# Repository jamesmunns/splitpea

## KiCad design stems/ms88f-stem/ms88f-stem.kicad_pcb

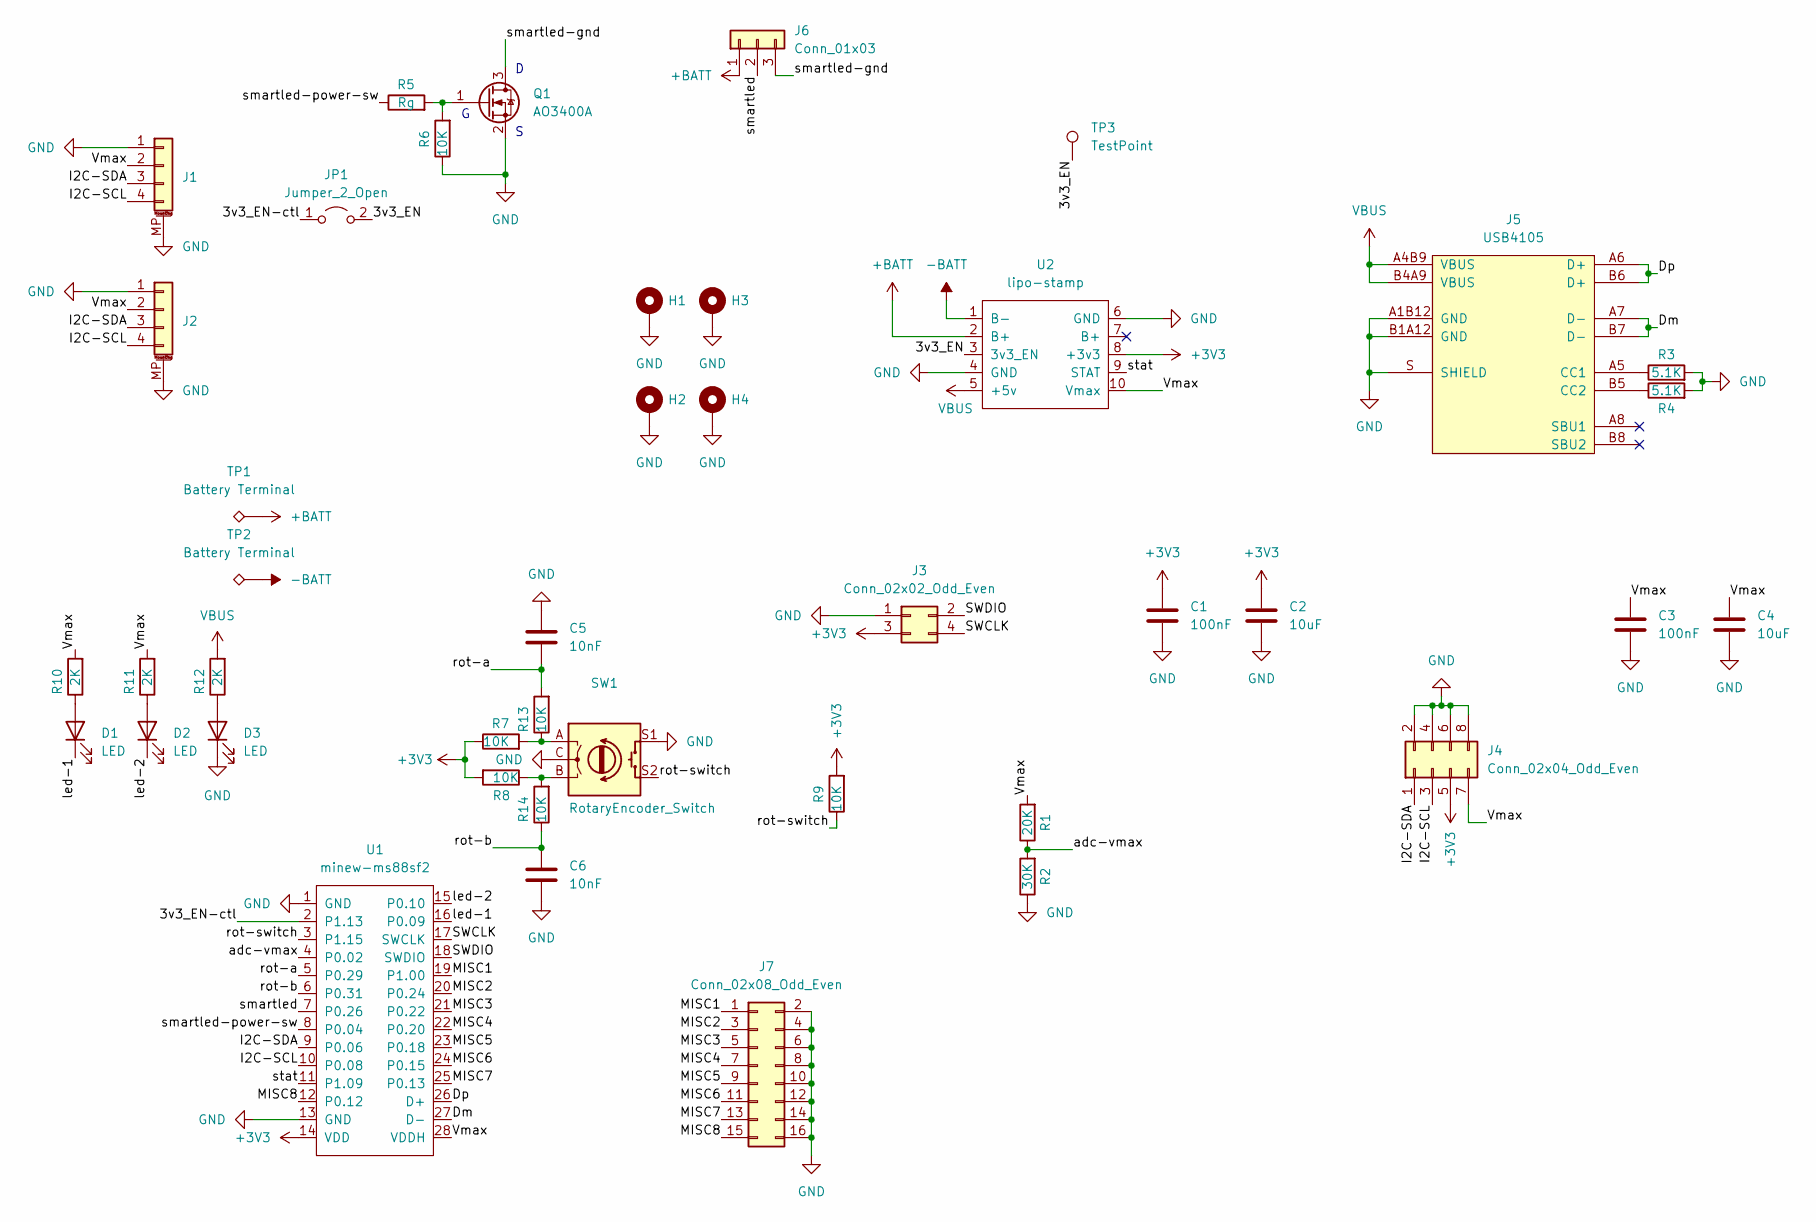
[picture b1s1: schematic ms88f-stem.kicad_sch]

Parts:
C1, C3: 100nF; C_0805_2012Metric
C2, C4: 10uF; C_0805_2012Metric
C5, C6: 10nF; C_0805_2012Metric
D1, D2, D3: LED; LED_0805_2012Metric
H1, H2, H3, H4: MountingHole_Pad; MountingHole_3.2mm_M3_Pad_Via
J1, J2: Conn_01x04_MountingPin; JST_SH_SM04B-SRSS-TB_1x04-1MP_P1.00mm_Horizontal
J3: Conn_02x02_Odd_Even; PinHeader_2x02_P2.54mm_Vertical_SMD
J4: Conn_02x04_Odd_Even; PinHeader_2x04_P2.54mm_Vertical
J5: USB4105; DigiKey 2073-USB4105-GF-ACT-ND
J6: Conn_01x03; PinHeader_1x03_P2.54mm_Horizontal
J7: Conn_02x08_Odd_Even; PinHeader_2x08_P2.54mm_Vertical
JP1: Jumper_2_Open; SolderJumper-2_P1.3mm_Open_TrianglePad1.0x1.5mm
Q1: AO3400A; SOT-23
R1: 20K; R_0805_2012Metric
R2: 30K; R_0805_2012Metric
R3, R4: 5.1K; R_0805_2012Metric
R5: Rg; R_0805_2012Metric
R6, R7, R8, R9, R13, R14: 10K; R_0805_2012Metric
R10, R11, R12: 2K; R_0805_2012Metric
SW1: RotaryEncoder_Switch; RotaryEncoder_Alps_EC11E-Switch_Vertical_H20mm
TP1, TP2: Battery Terminal; keystone-54
TP3: TestPoint; TestPoint_Pad_1.5x1.5mm
U1: minew-ms88sf2; minew-MS88SF21
U2: lipo-stamp

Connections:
+3V3: C1.1, C2.1, J3.3, J4.5, R7.1, R8.2, R9.2, U1.14 (VDD), U2.8 (+3v3)
+BATT: J6.1, TP1.1, U2.2 (B+)
-BATT: TP2.1, U2.1 (B-)
/3v3_EN: JP1.2 (B), TP3.1, U2.3 (3v3_EN)
/3v3_EN-ctl: JP1.1 (A), U1.2 (P1.13)
/Dm: J5.A7 (D-), J5.B7 (D-), U1.27 (D-)
/Dp: J5.A6 (D+), J5.B6 (D+), U1.26 (D+)
/I2C-SCL: J1.4, J2.4, J4.3, U1.10 (P0.08)
/I2C-SDA: J1.3, J2.3, J4.1, U1.9 (P0.06)
/MISC1: J7.1, U1.19 (P1.00)
/MISC2: J7.3, U1.20 (P0.24)
/MISC3: J7.5, U1.21 (P0.22)
/MISC4: J7.7, U1.22 (P0.20)
/MISC5: J7.9, U1.23 (P0.18)
/MISC6: J7.11, U1.24 (P0.15)
/MISC7: J7.13, U1.25 (P0.13)
/MISC8: J7.15, U1.12 (P0.12)
/SWCLK: J3.4, U1.17 (SWCLK)
/SWDIO: J3.2, U1.18 (SWDIO)
/Vmax: C3.1, C4.1, J1.2, J2.2, J4.7, R1.2, R10.2, R11.2, U1.28 (VDDH), U2.10 (Vmax)
/adc-vmax: R1.1, R2.2, U1.4 (P0.02)
/led-1: D1.1 (K), U1.16 (P0.09)
/led-2: D2.1 (K), U1.15 (P0.10)
/rot-a: C5.1, R13.2, U1.5 (P0.29)
/rot-b: C6.1, R14.1, U1.6 (P0.31)
/rot-switch: R9.1, SW1.S2, U1.3 (P1.15)
/smartled: J6.2, U1.7 (P0.26)
/smartled-gnd: J6.3, Q1.3 (D)
/smartled-power-sw: R5.1, U1.8 (P0.04)
/stat: U1.11 (P1.09), U2.9 (STAT)
GND: C1.2, C2.2, C3.2, C4.2, C5.2, C6.2, D3.1 (K), H1.1, H2.1, H3.1, H4.1, J1.1, J1.MP (MountPin), J2.1, J2.MP (MountPin), J3.1, J4.2, J4.4, J4.6, J4.8, J5.A1B12 (GND), J5.B1A12 (GND), J5.S (SHIELD), J7.2, J7.4, J7.6, J7.8, J7.10, J7.12, J7.14, J7.16, Q1.2 (S), R2.1, R3.2, R4.2, R6.1, SW1.C, SW1.S1, U1.1 (GND), U1.13 (GND), U2.4 (GND), U2.6 (GND)
unnamed: D1.2 (A), R10.1
unnamed: D2.2 (A), R11.1
unnamed: D3.2 (A), R12.1
unnamed: J5.A5 (CC1), R3.1
unnamed: J5.B5 (CC2), R4.1
unnamed: Q1.1 (G), R5.2, R6.2
unnamed: R7.2, R13.1, SW1.A
unnamed: R8.1, R14.2, SW1.B
VBUS: J5.A4B9 (VBUS), J5.B4A9 (VBUS), R12.2, U2.5 (+5v)

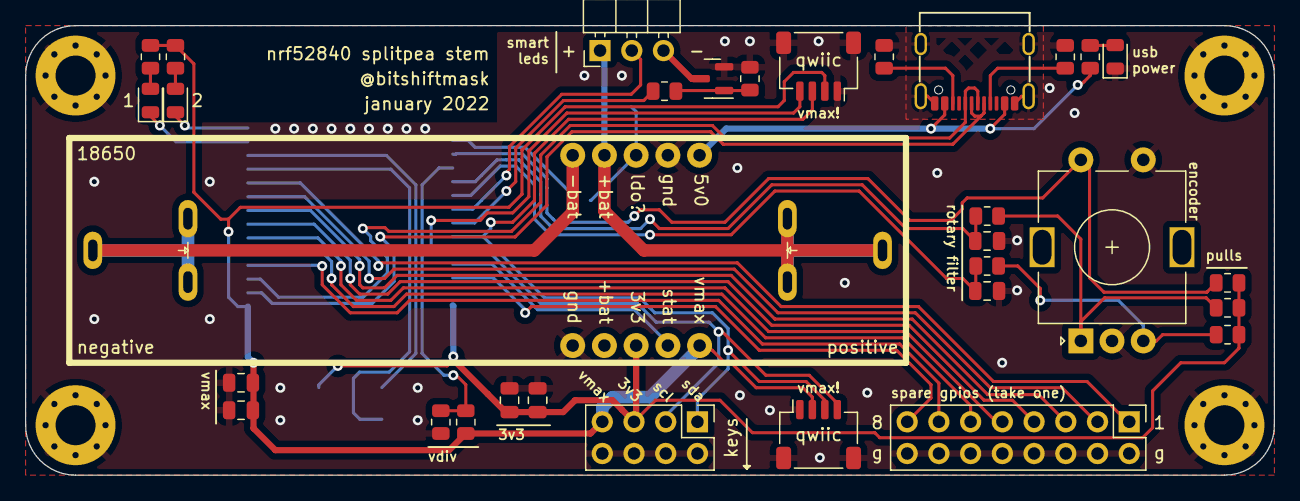
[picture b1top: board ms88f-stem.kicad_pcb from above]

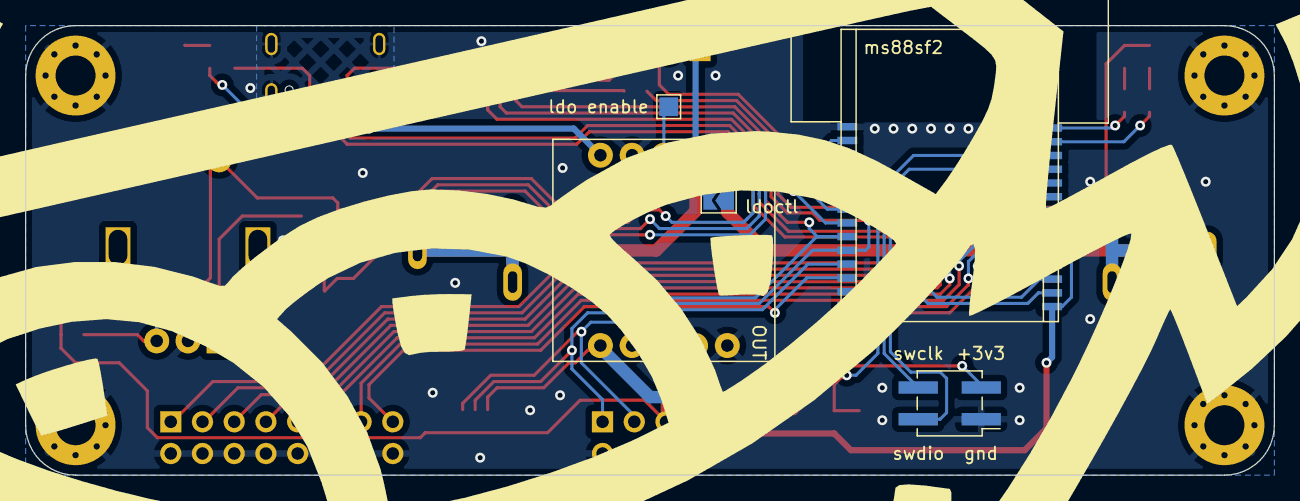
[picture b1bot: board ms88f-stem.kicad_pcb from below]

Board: 2 copper layers, 100.0 x 36.0 mm, 42 parts (5 on the bottom side), 40 nets.

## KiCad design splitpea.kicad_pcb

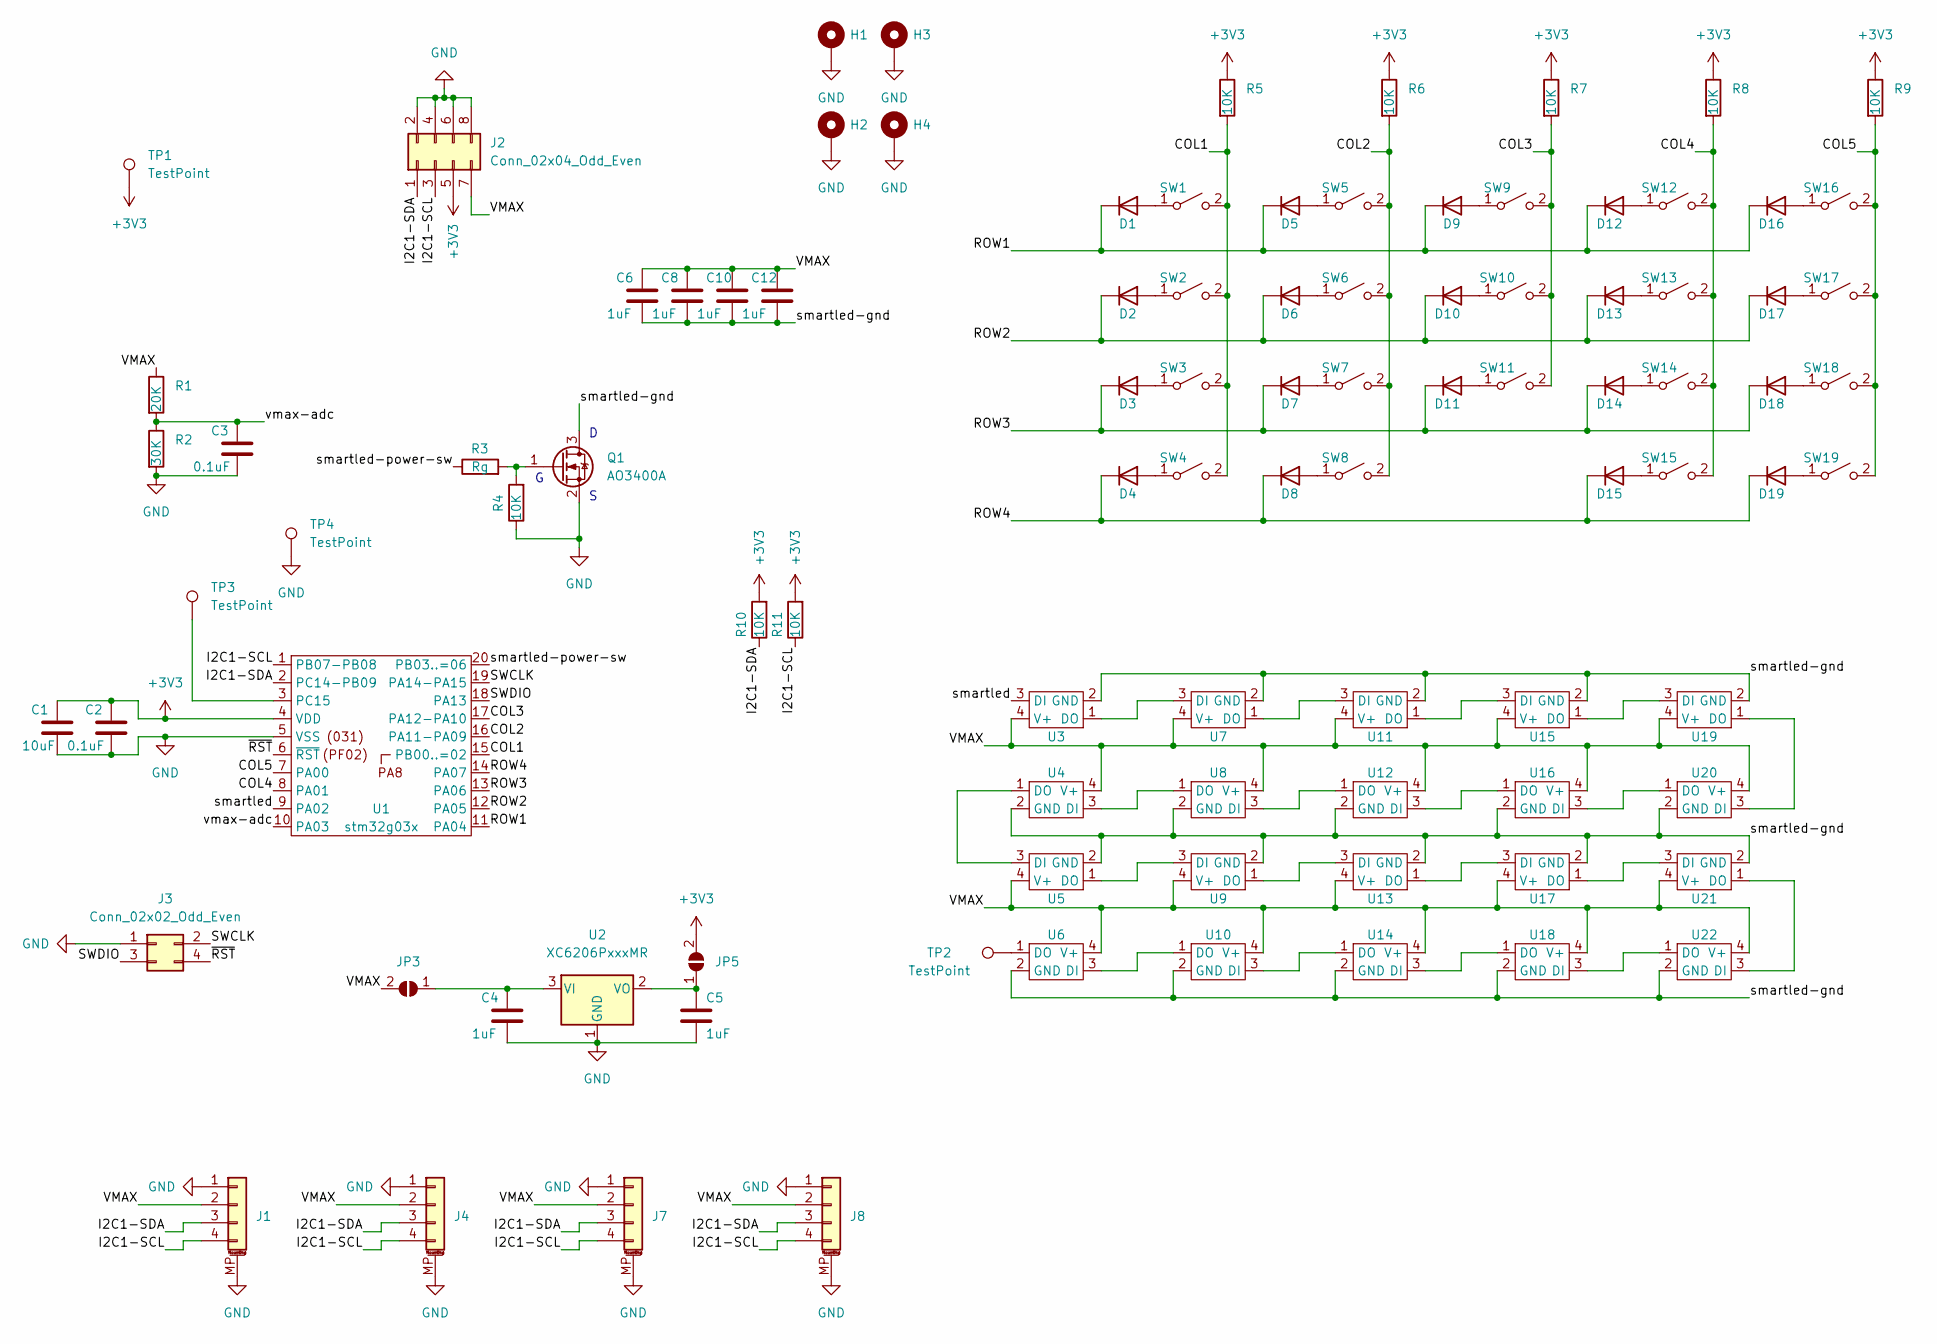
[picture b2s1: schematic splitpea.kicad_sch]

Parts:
C1: 10uF; C_0805_2012Metric
C2, C3: 0.1uF; C_0805_2012Metric
C4, C5, C6, C8, C10, C12: 1uF; C_0805_2012Metric
D1, D2, D3, D4, D5, D6, D7, D8, D9, D10, D11, D12, D13, D14, D15, D16, D17, D18, D19: D; D_SOD-123
H1, H2, H3, H4: MountingHole_Pad; MountingHole_3.2mm_M3_Pad_Via
J1, J4, J7, J8: Conn_01x04_MountingPin; JST_SH_SM04B-SRSS-TB_1x04-1MP_P1.00mm_Horizontal
J2: Conn_02x04_Odd_Even; PinHeader_2x04_P2.54mm_Vertical
J3: Conn_02x02_Odd_Even; PinHeader_2x02_P2.54mm_Vertical_SMD
JP3, JP5: SolderJumper_2_Open; SolderJumper-2_P1.3mm_Open_TrianglePad1.0x1.5mm
Q1: AO3400A; SOT-23
R1: 20K; R_0805_2012Metric
R2: 30K; R_0805_2012Metric
R3: Rg; R_0805_2012Metric
R4, R5, R6, R7, R8, R9, R10, R11: 10K; R_0805_2012Metric
SW1, SW2, SW3, SW4, SW5, SW6, SW7, SW8, SW9, SW10, SW11, SW12, SW13, SW14, SW15, SW16, SW17, SW18, SW19: SW_SPST; PG1350_socket
TP1, TP2, TP3, TP4: TestPoint; TestPoint_Pad_D1.5mm
U1: stm32g03x; SOIC65P640X120-20N
U2: XC6206PxxxMR; SOT-23
U3, U4, U5, U6, U7, U8, U9, U10, U11, U12, U13, U14, U15, U16, U17, U18, U19, U20, U21, U22: WS2812-2020-micro; LED_WS2812-2020

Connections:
+3V3: C1.1, C2.1, J2.5, JP5.2 (B), R5.1, R6.1, R7.1, R8.1, R9.1, R10.2, R11.2, TP1.1, U1.4 (VDD)
/COL1: R5.2, SW1.2 (B), SW2.2 (B), SW3.2 (B), SW4.2 (B), U1.15 (PB00..=02)
/COL2: R6.2, SW5.2 (B), SW6.2 (B), SW7.2 (B), SW8.2 (B), U1.16 (PA11-PA09)
/COL3: R7.2, SW9.2 (B), SW10.2 (B), SW11.2 (B), U1.17 (PA12-PA10)
/COL4: R8.2, SW12.2 (B), SW13.2 (B), SW14.2 (B), SW15.2 (B), U1.8 (PA01)
/COL5: R9.2, SW16.2 (B), SW17.2 (B), SW18.2 (B), SW19.2 (B), U1.7 (PA00)
/I2C1-SCL: J1.4, J2.3, J4.4, J7.4, J8.4, R11.1, U1.1 (PB07-PB08)
/I2C1-SDA: J1.3, J2.1, J4.3, J7.3, J8.3, R10.1, U1.2 (PC14-PB09)
/ROW1: D1.1 (K), D5.1 (K), D9.1 (K), D12.1 (K), D16.1 (K), U1.11 (PA04)
/ROW2: D2.1 (K), D6.1 (K), D10.1 (K), D13.1 (K), D17.1 (K), U1.12 (PA05)
/ROW3: D3.1 (K), D7.1 (K), D11.1 (K), D14.1 (K), D18.1 (K), U1.13 (PA06)
/ROW4: D4.1 (K), D8.1 (K), D15.1 (K), D19.1 (K), U1.14 (PA07)
/SWCLK: J3.2, U1.19 (PA14-PA15)
/SWDIO: J3.3, U1.18 (PA13)
/VMAX: C6.1, C8.1, C10.1, C12.1, J1.2, J2.7, J4.2, J7.2, J8.2, JP3.2 (B), R1.1, U3.4 (V+), U4.4 (V+), U5.4 (V+), U6.4 (V+), U7.4 (V+), U8.4 (V+), U9.4 (V+), U10.4 (V+), U11.4 (V+), U12.4 (V+), U13.4 (V+), U14.4 (V+), U15.4 (V+), U16.4 (V+), U17.4 (V+), U18.4 (V+), U19.4 (V+), U20.4 (V+), U21.4 (V+), U22.4 (V+)
/smartled: U1.9 (PA02), U3.3 (DI)
/smartled-gnd: C6.2, C8.2, C10.2, C12.2, Q1.3 (D), U3.2 (GND), U4.2 (GND), U5.2 (GND), U6.2 (GND), U7.2 (GND), U8.2 (GND), U9.2 (GND), U10.2 (GND), U11.2 (GND), U12.2 (GND), U13.2 (GND), U14.2 (GND), U15.2 (GND), U16.2 (GND), U17.2 (GND), U18.2 (GND), U19.2 (GND), U20.2 (GND), U21.2 (GND), U22.2 (GND)
/smartled-power-sw: R3.1, U1.20 (PB03..=06)
/vmax-adc: C3.1, R1.2, R2.1, U1.10 (PA03)
/~RST: J3.4, U1.6 (~RST)
GND: C1.2, C2.2, C3.2, C4.2, C5.2, H1.1, H2.1, H3.1, H4.1, J1.1, J1.MP (MountPin), J2.2, J2.4, J2.6, J2.8, J3.1, J4.1, J4.MP (MountPin), J7.1, J7.MP (MountPin), J8.1, J8.MP (MountPin), Q1.2 (S), R2.2, R4.1, TP4.1, U1.5 (VSS), U2.1 (GND)
unnamed: C4.1, JP3.1 (A), U2.3 (VI)
unnamed: C5.1, JP5.1 (A), U2.2 (VO)
unnamed: D1.2 (A), SW1.1 (A)
unnamed: D2.2 (A), SW2.1 (A)
unnamed: D3.2 (A), SW3.1 (A)
unnamed: D4.2 (A), SW4.1 (A)
unnamed: D5.2 (A), SW5.1 (A)
unnamed: D6.2 (A), SW6.1 (A)
unnamed: D7.2 (A), SW7.1 (A)
unnamed: D8.2 (A), SW8.1 (A)
unnamed: D9.2 (A), SW9.1 (A)
unnamed: D10.2 (A), SW10.1 (A)
unnamed: D11.2 (A), SW11.1 (A)
unnamed: D12.2 (A), SW12.1 (A)
unnamed: D13.2 (A), SW13.1 (A)
unnamed: D14.2 (A), SW14.1 (A)
unnamed: D15.2 (A), SW15.1 (A)
unnamed: D16.2 (A), SW16.1 (A)
unnamed: D17.2 (A), SW17.1 (A)
unnamed: D18.2 (A), SW18.1 (A)
unnamed: D19.2 (A), SW19.1 (A)
unnamed: Q1.1 (G), R3.2, R4.2
unnamed: TP3.1, U1.3 (PC15)
unnamed: U3.1 (DO), U7.3 (DI)
unnamed: U4.1 (DO), U5.3 (DI)
unnamed: U4.3 (DI), U8.1 (DO)
unnamed: U5.1 (DO), U9.3 (DI)
unnamed: TP2.1, U6.1 (DO)
unnamed: U6.3 (DI), U10.1 (DO)
unnamed: U10.3 (DI), U14.1 (DO)
unnamed: U11.1 (DO), U15.3 (DI)
unnamed: U7.1 (DO), U11.3 (DI)
unnamed: U8.3 (DI), U12.1 (DO)
unnamed: U12.3 (DI), U16.1 (DO)
unnamed: U13.1 (DO), U17.3 (DI)
unnamed: U9.1 (DO), U13.3 (DI)
unnamed: U14.3 (DI), U18.1 (DO)
unnamed: U15.1 (DO), U19.3 (DI)
unnamed: U16.3 (DI), U20.1 (DO)
unnamed: U17.1 (DO), U21.3 (DI)
unnamed: U18.3 (DI), U22.1 (DO)
unnamed: U19.1 (DO), U20.3 (DI)
unnamed: U21.1 (DO), U22.3 (DI)

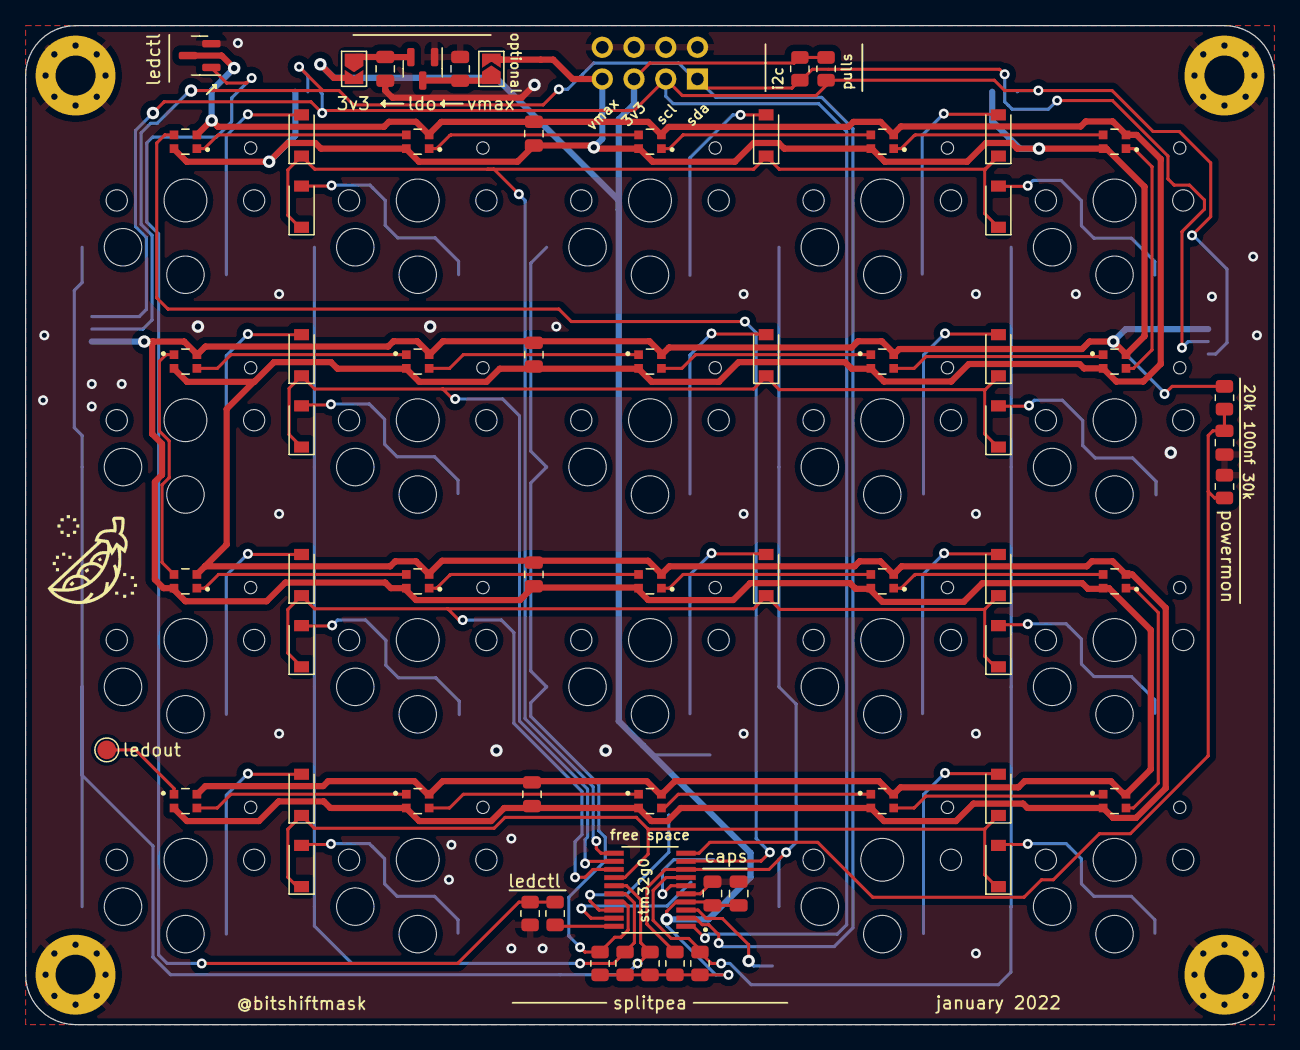
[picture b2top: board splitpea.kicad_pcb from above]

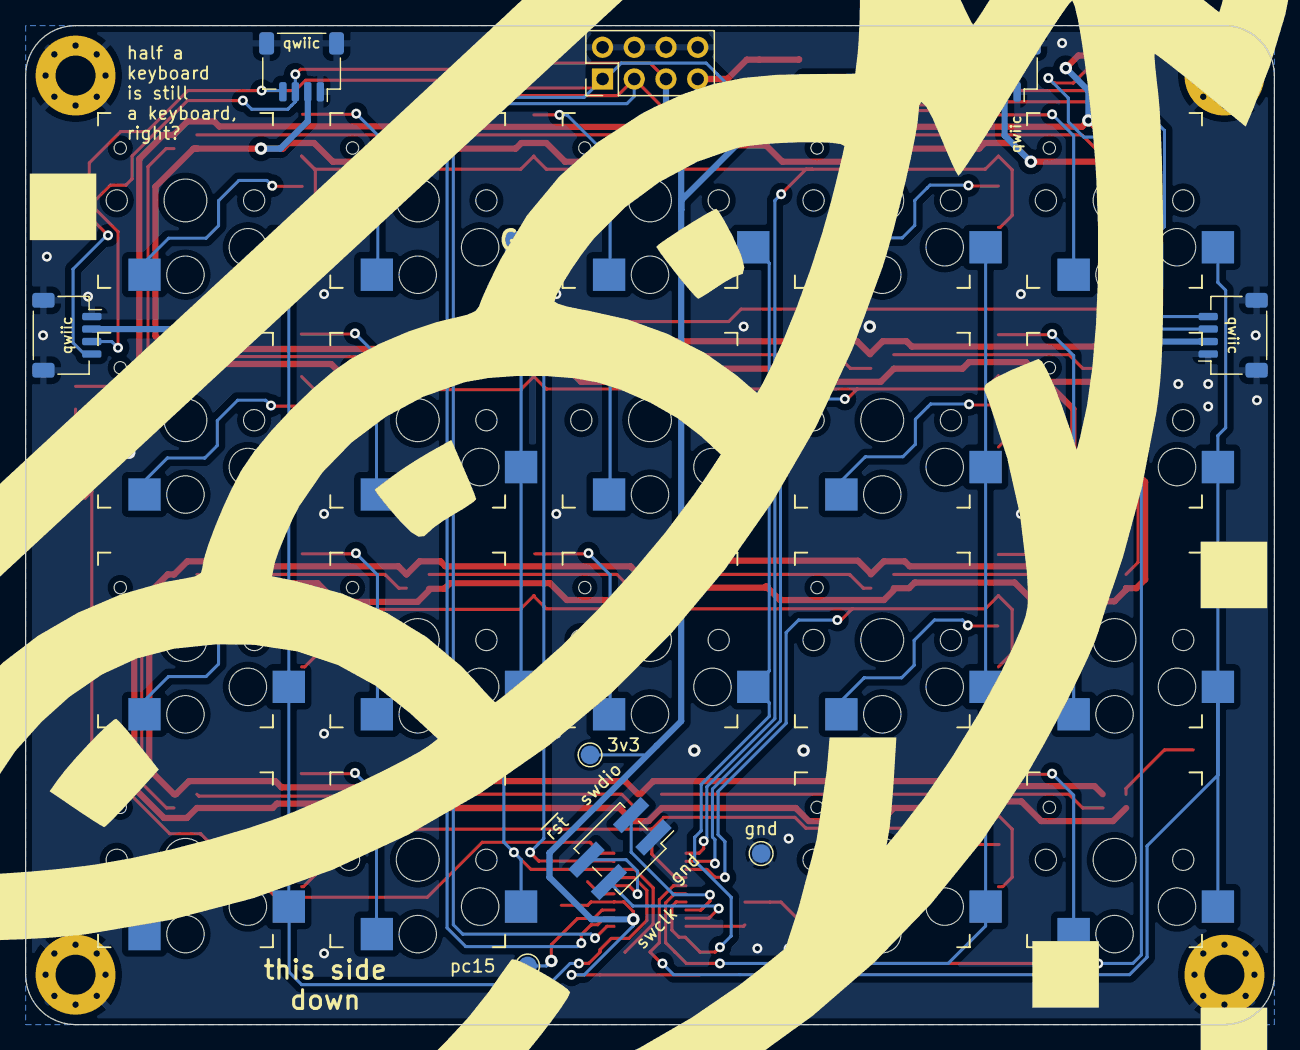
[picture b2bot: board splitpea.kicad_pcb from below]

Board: 2 copper layers, 100.0 x 80.0 mm, 97 parts (9 on the bottom side), 64 nets.

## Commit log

2022-01-18 Mostly done...
2022-01-19 Add stem
